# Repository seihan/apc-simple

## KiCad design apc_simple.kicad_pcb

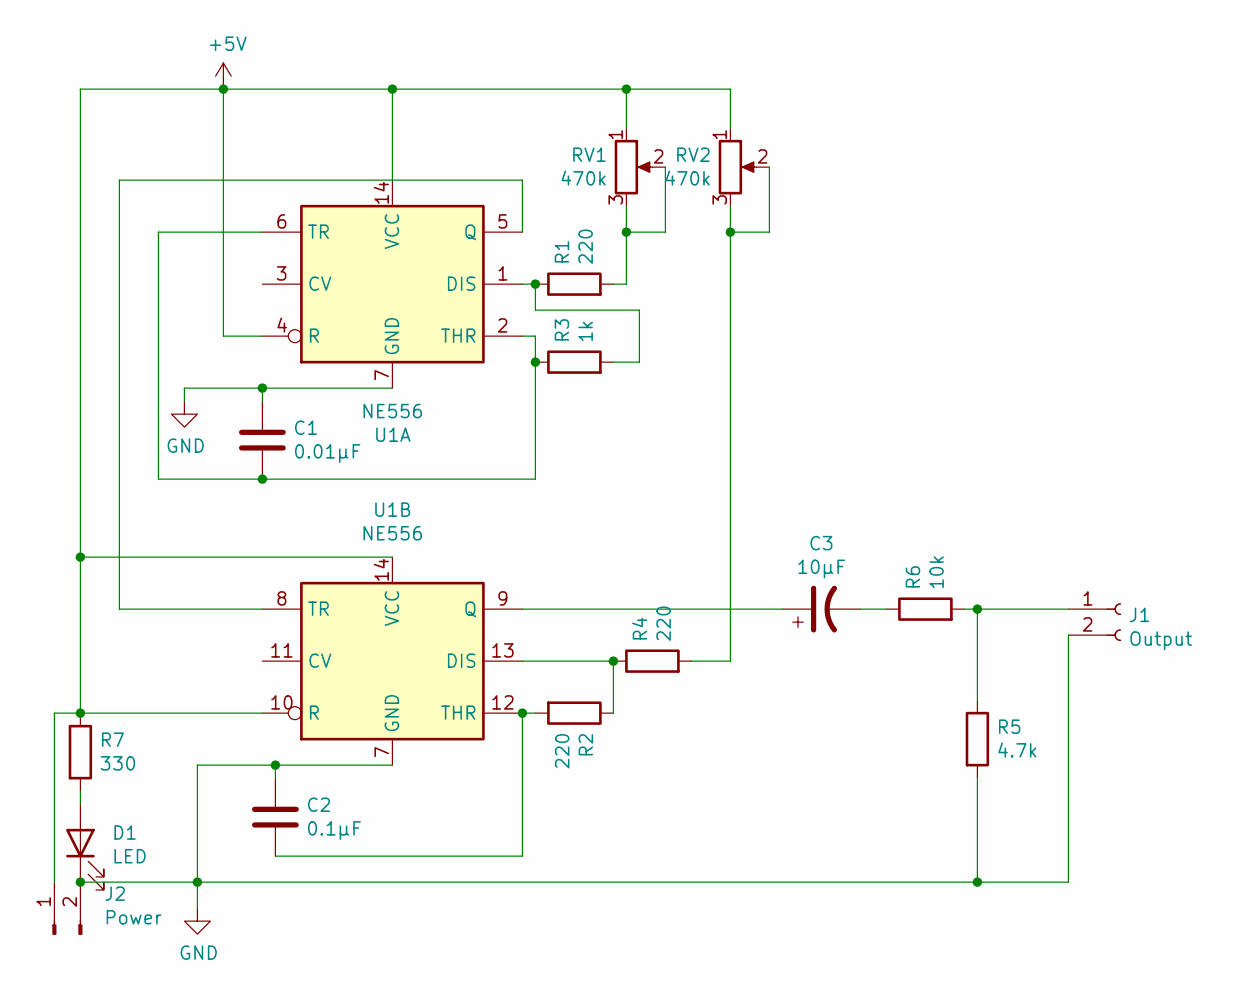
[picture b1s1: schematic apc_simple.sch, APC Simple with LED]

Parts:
C1: 0.01µF; C_Rect_L4.0mm_W2.5mm_P2.50mm
C2: 0.1µF; C_Rect_L7.0mm_W2.0mm_P5.00mm
C3: 10µF; CP_Radial_Tantal_D4.5mm_P2.50mm
D1: LED; LED_D5.0mm
J1: Output; PinHeader_1x02_P2.54mm_Vertical
J2: Power; PinHeader_1x03_P2.54mm_Vertical
R1, R2, R4: 220; R_Axial_DIN0411_L9.9mm_D3.6mm_P12.70mm_Horizontal
R3: 1k; R_Axial_DIN0411_L9.9mm_D3.6mm_P12.70mm_Horizontal
R5: 4.7k; R_Axial_DIN0411_L9.9mm_D3.6mm_P12.70mm_Horizontal
R6: 10k; R_Axial_DIN0411_L9.9mm_D3.6mm_P12.70mm_Horizontal
R7: 330; R_Axial_DIN0411_L9.9mm_D3.6mm_P12.70mm_Horizontal
RV1, RV2: 470k; Potentiometer_Piher_T-16H_Single_Horizontal
U1: NE556; DIP-14_W7.62mm_Socket

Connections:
+5V: J2.1, R7.1, RV1.1, RV2.1, U1.4 (R), U1.10 (R), U1.14 (VCC)
GND: C1.1, C2.1, D1.1 (K), J1.2, J2.2, R5.2, U1.7 (GND)
unnamed: C1.2, R3.1, U1.2 (THR), U1.6 (TR)
unnamed: C2.2, R2.2, U1.12 (THR)
unnamed: C3.1, U1.9 (Q)
unnamed: C3.2, R6.1
unnamed: D1.2 (A), R7.2
unnamed: J1.1, R5.1, R6.2
unnamed: R1.1, R3.2, U1.1 (DIS)
unnamed: R1.2, RV1.2, RV1.3
unnamed: R2.1, R4.1, U1.13 (DIS)
unnamed: R4.2, RV2.2, RV2.3
unnamed: U1.5 (Q), U1.8 (TR)

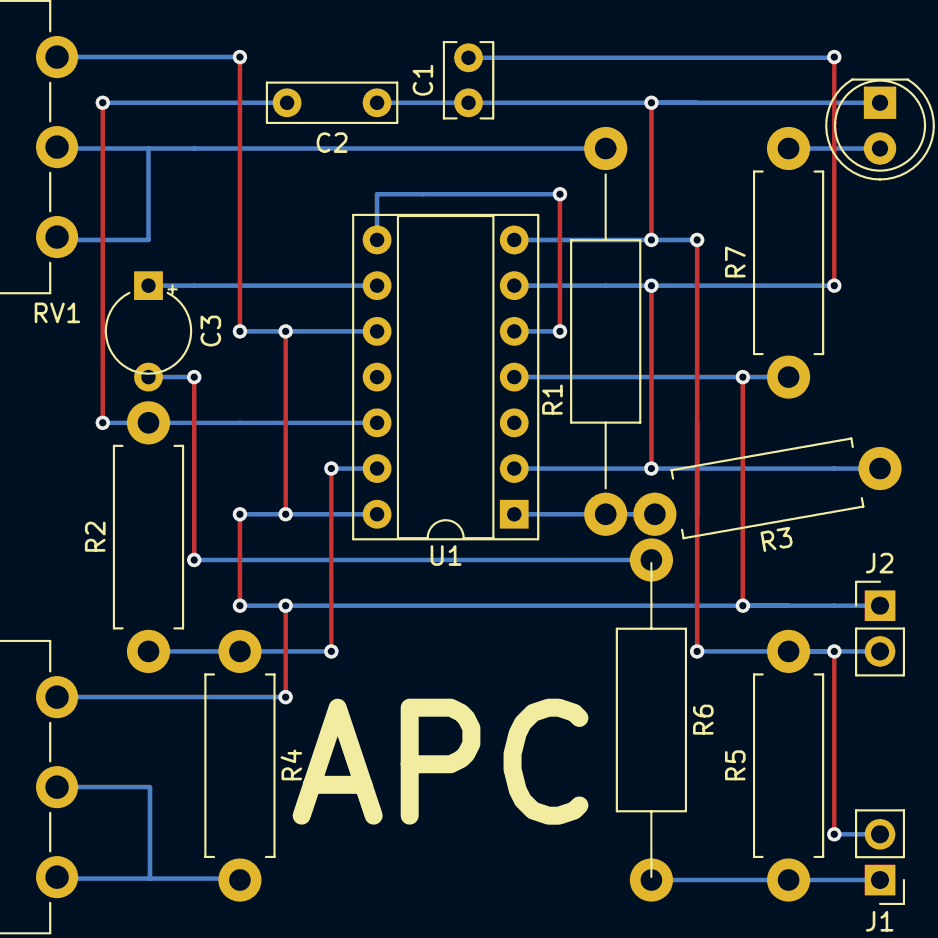
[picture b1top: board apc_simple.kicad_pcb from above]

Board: 2 copper layers, 16 parts (0 on the bottom side), 13 nets.

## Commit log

2022-07-03 init
2022-08-06 Fixed error in schematic; re-designed breadboard wiring
2022-08-06 Rewire 1k resistor directly between THR and DIS
2022-08-07 pcb: reroute for strip mask pattern
    Adapt some resistor footprints to indicate better
    where they are used to bridge connections. Make
    every upper layer wire bridge standalone.
2022-08-07 Make it fit 19x19 strip mask
    Switch around some connectors and footprints.
    Mark strip mask lane cutting marks on backside "silk screen".
2022-08-08 pcb: move pads to correct position
    Modify C3, R3 and R6 footprints to match the
    intended placement on a strip board.
2022-08-08 pcb: resize margin of board
2022-08-08 pcb: rearrange cutmarks, add wire shorts
    Some places are easier just to short on the backside.
    This saves some wire bridges and allows to place cut
    indicators a little better aligned.
    Also add an 'APC' text by squishing resistors R4 and
    R6 a little to the side.
2022-08-08 Refresh PDFs
